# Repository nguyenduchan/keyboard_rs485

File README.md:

# Bàn phím công nghiệp All-in-One (PCB 120 × 120 mm)

Mạch **STM32G030F6P6 + RS485 (SIT3485)**, rev C — linh kiện phổ biến. **TM1638** quét 2 module LED 4 số, 8 LED trạng thái và 16 phím. Còi chủ động báo nhận phím. **Mặt trên (F.Cu):** toàn bộ **chip và SMD**, stencil một lần. **Mặt dưới (B.Cu):** chỉ **phím, LED 3 mm, 2 module 7 đoạn 4 số**. PCB đã đi dây 2 lớp (autorouter PathFinder, `tools/pathfinder.cpp`), DRC KiCad sạch. Cột phải tách **nguồn (trên)** và **MCU + RS485 (dưới)**. Chống phím ma: `docs/CHONG_PHIM_MA.md`.

## Cấu trúc thư mục

| Thư mục / file | Nội dung |
|----------------|----------|
| `docs/SO_DO_NGUYEN_LY.md` | Sơ đồ nguyên lý, ghép chân, netlist |
| `docs/PCB_LAYOUT.md` | Tọa độ mm, mặt trên / mặt dưới, checklist |
| `docs/CHONG_PHIM_MA.md` | Lọc ma trận, tách vùng nguồn |
| `hardware/kicad/panel-keyboard/tools/front_layout_spec.py` | **Chuẩn tọa độ mặt trước** |
| `docs/CONFIG_PROTOCOL.md`, `docs/RUNTIME_FORMAT.md` | giao thức cấu hình + bản đồ thanh ghi + khối cấu hình (cho PC app) |
| `firmware/` | firmware STM32G030F6P6 (xem `firmware/README.md`) |
| `hardware/bom.csv` | BOM |

## Đồng bộ schematic + PCB

```text
python hardware/kicad/panel-keyboard/tools/update_pcb_all.py
python hardware/kicad/panel-keyboard/tools/verify_front_layout.py
```

`update_pcb_all.py` gọi `migrate_front_tht.py` (một process/ref, tránh crash `pcbnew` trên Windows) rồi `fix_front_layout.py` + gán net.

(Đóng KiCad trước khi chạy.) Quy tắc: `.cursor/rules/kicad-schematic-pcb-sync.mdc`

---

## Phím và LED — mặt dưới (B.Cu)

KiCad vẽ trang với **Y tăng xuống dưới** (đỉnh hình = Y nhỏ). Từ trên xuống: **7-seg → khe CNC 8 mm → keypad**. LED trạng thái ở cột phải của cụm phím. Thân phím và LED hướng xuống mặt dưới.

Hai module 4 số 0,56" (5641AS, thân 50,4 × 19,0 mm, bước digit 12,7 mm) đặt tâm **X=40** trùng tâm keypad. Hàng chân cách 15,24 mm. Khe giữa mép dưới thân 7-seg và mép trên thân phím là **8 mm**.

| Y | 16 | 32 | 48 | 64 | | 80 |
|---:|:---:|:---:|:---:|:---:|:---|:---:|
| 12 | | | | | | D10 |
| 15 | DS1 module 4 số (digit 1–4, tâm X=40) | | | | | |
| 20 | | | | | | D11 |
| 28 | | | | | | D12 |
| 35 | DS2 module 4 số (digit 5–8, tâm X=40) | | | | | |
| 36 | | | | | | D13 |
| 44 | | | | | | D14 |
| 52 | | | | | | D15 |
| 59 | SW13 | SW14 | SW15 | SW16 | | |
| 60 | | | | | | D16 |
| 68 | | | | | | D17 |
| 75 | SW9 | SW10 | SW11 | SW12 | | |
| 91 | SW5 | SW6 | SW7 | SW8 | | |
| 107 | SW1 | SW2 | SW3 | SW4 | | |

### Kiểm tra layout

Script so PCB với `front_layout_spec.py` (dung sai **0,01 mm** — lỗ phay mặt tủ tính từ tọa độ này):

```text
python hardware/kicad/panel-keyboard/tools/verify_front_layout.py
```

Tiêu chí:

- 16 nút + 2 module 4 số + 8 LED đúng tọa độ  
- Khe **thân phím ↔ thân module 7-seg dưới (DS2)** ≥ **8 mm** (đủ lưỡi CNC khoảng 3 mm và gân mặt máy)

Chuẩn hóa footprint trên PCB: `tools/fix_front_layout.py` (sau `update_pcb_all.py`).

---

## Chip và SMD — mặt trên (F.Cu)

**U6 TM1638** (SOP-28) nằm dưới cột LED trạng thái, quét 7-seg, LED 3 mm và phím. **U1 STM32G030F6P6** ngay bên phải, nối 3 dây STB/CLK/DIO (kéo lên 4,7k). Còi **BZ1** mặt trên tại (40, 50). Cột phải **X ≈ 82…118** tách hai khối: nguồn phía trên, MCU + RS485 phía dưới. **J_PWR** (115, 16) và **J485** (115, 102) hướng ra **cạnh phải**.

| Vùng | X (mm) | Y (mm) | Nội dung |
|------|--------|--------|----------|
| Dưới LED trạng thái | 70–90 | 74–99 | U6 TM1638, CLED1–3, RSTB/RCLK/RDIO |
| MCU | 90–104 | 80–96 | U1, CVDD1, CNRST, J_SWD và J_LOG (không lắp) |
| Còi | 34–58 | 44–56 | BZ1, QBZ, RBZG |
| **BUCK_5V** | 82–118 | 4–46 | J_PWR, U4 XL1509 (SOP-8), L1, D8, C2, C22 |
| **24V_PROTECT** | 82–118 | 48–76 | C4, F1, FBIN, TVS1, DREV, U5 |
| **MCU_LOGIC** | 72–118 | 78–116 | U1, U3, J485 |

Chi tiết: `docs/PCB_LAYOUT.md`, `tools/zone_layout.py`.

---

## Cơ khí tủ

- Lỗ phay mặt tủ **theo biến thể** (số module 7 đoạn, số LED, số phím / bàn phím màng), mọi số đo nguyên mm, nhìn từ mặt tủ: `hardware/mechanical/cnc/` (DXF cho máy CNC, SVG, CSV, decal). Sinh và kiểm tra: `python hardware/kicad/panel-keyboard/tools/cnc_panel.py --check` — xem `docs/CNC_MAT_MAY.md`.  
- Chip nằm **mặt trên**. Mặt dưới chỉ có phím và LED, hướng ra mặt máy  

## Mở thiết kế

KiCad 10+: `hardware/kicad/panel-keyboard/panel-keyboard.kicad_pro`

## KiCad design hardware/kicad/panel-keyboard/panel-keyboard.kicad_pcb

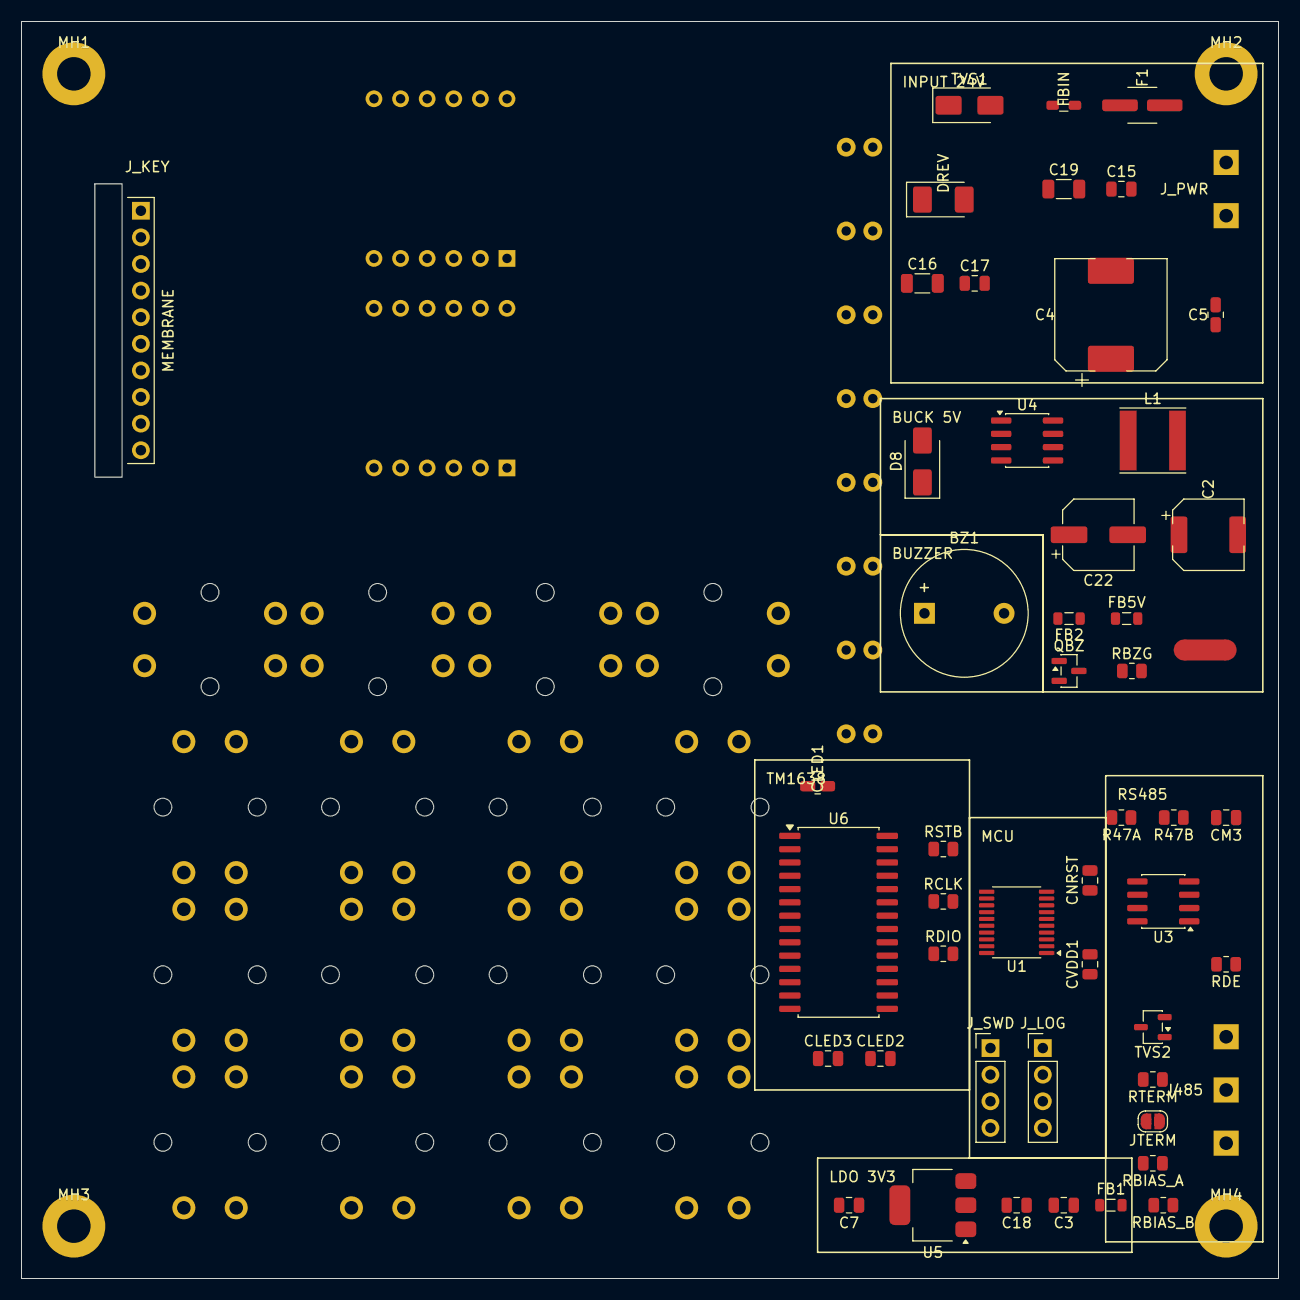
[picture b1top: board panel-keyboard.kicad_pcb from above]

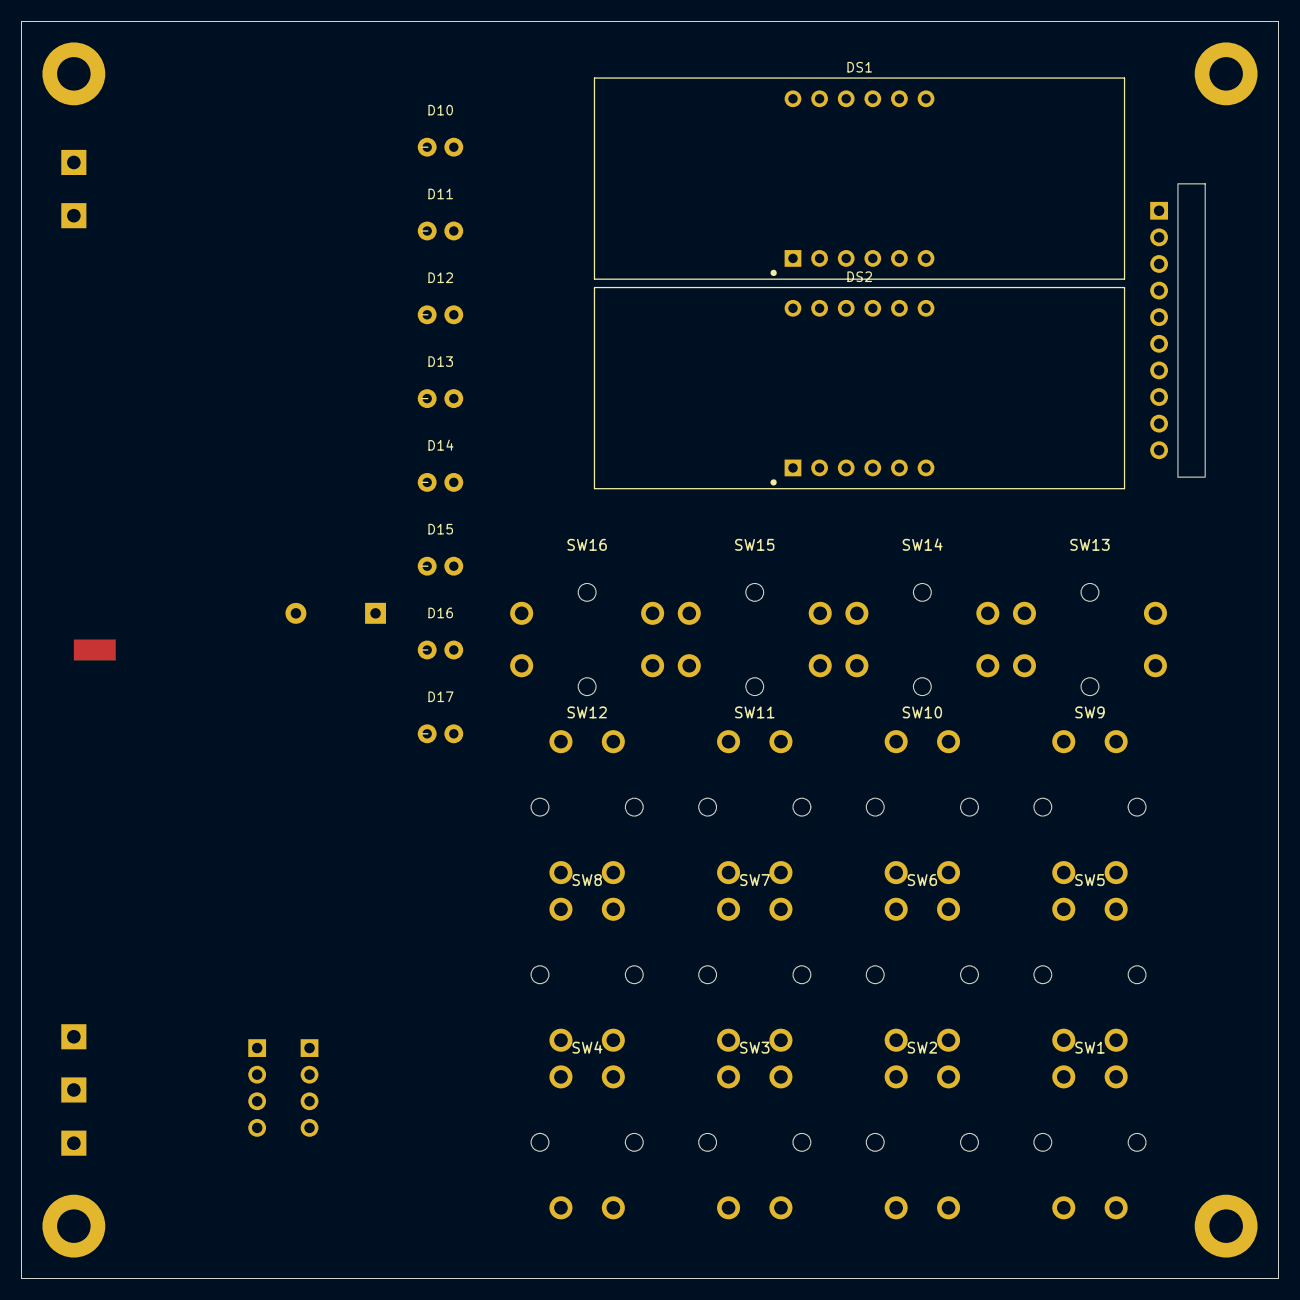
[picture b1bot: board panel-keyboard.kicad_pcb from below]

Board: 2 copper layers, 120.0 x 120.0 mm, 81 parts (26 on the bottom side), 49 nets, no tracks yet.

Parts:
BZ1: Active buzzer 5V 12x9.5; Buzzer_12x9.5RM7.6
C2, C22: 220uF 10V RVT1A221M0605; CP_Elec_6.3x5.4
C3: 22uF; C_0805_2012Metric
C4: 470uF 35V RVT1V471M1010; CP_Elec_10x10.5
C5, C18: 100nF; C_0805_2012Metric
C7: 10uF; C_0805_2012Metric
C15, C17: 100nF 50V; C_0805_2012Metric
C16, C19: 2.2uF 50V X7R; C_1206_3216Metric
CLED1, CLED2: 100nF; C_0805_2012Metric
CLED3: 10uF; C_0805_2012Metric
CM3: 100nF; C_0805_2012Metric
CNRST: 100nF; C_0805_2012Metric
CVDD1: 100nF; C_0805_2012Metric
D8: SS34; D_SMA
D10, D11, D12, D13, D14, D15, D16, D17: LED_3mm; LED_3mm_THT
DREV: SS34; D_SMA
DS1, DS2: 5641AS (4 digit 0.56in CC); Display_4digit_0.56in_THT
F1: mSMD050-33V (PPTC 0.5A 33V); Fuse_1812_4532Metric
FB1, FB2, FB5V: GZ2012D101TF 100R; L_0805_2012Metric
FBIN: GZ2012D601TF 600R; L_0805_2012Metric
J485: KF301-5.08-3P; TerminalBlock_3P_5.08
JTERM: 120R; SolderJumper-2_P1.3mm_Open_RoundedPad1.0x1.5mm
J_KEY: Membrane 1x10 2.54; Membrane_1x10_P2.54_Vertical_Slot
J_LOG: PinHeader_1x04_P2.54mm_Vertical
J_PWR: KF301-5.08-2P; TerminalBlock_2P_5.08
J_SWD: PinHeader_1x04_P2.54mm_Vertical
L1: SWPA6045S470MT 47uH; L_Taiyo-Yuden_NR-60xx
MH1, MH2, MH3, MH4: M3; MountingHole_M3
NT1: GND_STAR; NetTie-2_SMD_Pad2.0mm
QBZ: 2N7002; SOT-23
R47A, R47B: 47; R_0805_2012Metric
RBIAS_A: 560; R_0805_2012Metric
RBIAS_B: 560; R_0805_2012Metric
RBZG: 100k; R_0805_2012Metric
RCLK: 4.7k; R_0805_2012Metric
RDE: 10k; R_0805_2012Metric
RDIO: 4.7k; R_0805_2012Metric
RSTB: 4.7k; R_0805_2012Metric
RTERM: 120; R_0805_2012Metric
SW1, SW2, SW3, SW4, SW5, SW6, SW7, SW8, SW9, SW10, SW11, SW12, SW13, SW14, SW15, SW16: B3F-4055; SW_Tactile_12mm_THT
TVS1: SMAJ28CA; D_SMA
TVS2: PSM712-LF-T7; SOT-23-3
U1: STM32G030F6P6; TSSOP-20_4.4x6.5mm_P0.65mm
U3: SP3485EN; SOIC-8_3.9x4.9mm_P1.27mm
U4: XL1509-5.0E1; SOIC-8_3.9x4.9mm_P1.27mm
U5: AMS1117-3.3; SOT-223-3_TabPin2
U6: TM1638; SOIC-28W_7.5x17.9mm_P1.27mm

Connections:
+3V3: CM3.1, CVDD1.1, FB1.2, J_LOG.1, J_SWD.1, U1.4, U3.8
+3V3_LDO: C3.1, C18.1, FB1.1, U5.2
+5V: BZ1.1, C7.1, C22.1, FB2.2, FB5V.1, RBIAS_A.1, U5.3
+5V_LED: CLED1.1, CLED2.1, CLED3.1, FB5V.2, RCLK.1, RDIO.1, RSTB.1, U6.4, U6.15
+5V_RAW: C2.1, C5.1, FB2.1, L1.2, U4.3
+5V_SW: D8.1, L1.1, U4.2
+24V: C4.1, C16.1, C17.1, DREV.1, U4.1
+24V_FUSE: F1.2, FBIN.1
+24V_IN: F1.1, J_PWR.1
BZ_DRV: BZ1.2, QBZ.3
BZ_ON: QBZ.1, RBZG.1, U1.14
GND: C2.2, C3.2, C5.2, C7.2, C18.2, C22.2, CLED1.2, CLED2.2, CLED3.2, CM3.2, CNRST.2, CVDD1.2, J485.3, J_LOG.4, J_SWD.4, NT1.2, QBZ.2, RBIAS_B.2, RBZG.2, RDE.2, TVS2.3, U1.5, U3.5, U5.1, U6.18, U6.25
GND_PWR: C4.2, C15.2, C16.2, C17.2, C19.2, D8.2, J_PWR.2, NT1.1, TVS1.2, U4.4, U4.5, U4.6, U4.7, U4.8
GRID_1: D10.1, DS1.12, U6.24
GRID_2: D11.1, DS1.9, U6.23
GRID_3: D12.1, DS1.8, U6.22
GRID_4: D13.1, DS1.6, U6.21
GRID_5: D14.1, DS2.12, U6.20
GRID_6: D15.1, DS2.9, U6.19
GRID_7: D16.1, DS2.8, U6.17
GRID_8: D17.1, DS2.6, U6.16
KEY_K1: J_KEY.1, SW1.2, SW1.3, SW2.2, SW2.3, SW3.2, SW3.3, SW4.2, SW4.3, SW5.2, SW5.3, SW6.2, SW6.3, SW7.2, SW7.3, SW8.2, SW8.3, U6.1
KEY_K2: J_KEY.2, SW9.2, SW9.3, SW10.2, SW10.3, SW11.2, SW11.3, SW12.2, SW12.3, SW13.2, SW13.3, SW14.2, SW14.3, SW15.2, SW15.3, SW16.2, SW16.3, U6.2
LED_ROW: D10.2, D11.2, D12.2, D13.2, D14.2, D15.2, D16.2, D17.2, U6.13
LOG_RX: J_LOG.3, U1.1
LOG_TX: J_LOG.2, U1.20
MAX_DI: R47A.2, U3.4
MAX_RO: R47B.2, U3.1
NRST: CNRST.1, U1.6
RS485_A_BUS: J485.1, JTERM.1, RBIAS_A.2, TVS2.1, U3.6
RS485_B_BUS: J485.2, RBIAS_B.1, RTERM.2, TVS2.2, U3.7
RS485_DE: RDE.1, U1.8, U3.2, U3.3
RS485_TERM: JTERM.2, RTERM.1
SEG1: DS1.11, DS2.11, J_KEY.3, SW1.1, SW1.4, SW9.1, SW9.4, U6.5
SEG2: DS1.7, DS2.7, J_KEY.4, SW2.1, SW2.4, SW10.1, SW10.4, U6.6
SEG3: DS1.4, DS2.4, J_KEY.5, SW3.1, SW3.4, SW11.1, SW11.4, U6.7
SEG4: DS1.2, DS2.2, J_KEY.6, SW4.1, SW4.4, SW12.1, SW12.4, U6.8
SEG5: DS1.1, DS2.1, J_KEY.7, SW5.1, SW5.4, SW13.1, SW13.4, U6.9
SEG6: DS1.10, DS2.10, J_KEY.8, SW6.1, SW6.4, SW14.1, SW14.4, U6.10
SEG7: DS1.5, DS2.5, J_KEY.9, SW7.1, SW7.4, SW15.1, SW15.4, U6.11
SEG8: DS1.3, DS2.3, J_KEY.10, SW8.1, SW8.4, SW16.1, SW16.4, U6.12
SWCLK: J_SWD.3, U1.19
SWDIO: J_SWD.2, U1.18
TM_CLK: RCLK.2, U1.12, U6.27
TM_DIO: RDIO.2, U1.13, U6.26
TM_STB: RSTB.2, U1.11, U6.28
UART_RX: R47B.1, U1.10
UART_TX: R47A.1, U1.9
VIN_PROTECT: C15.1, C19.1, DREV.2, FBIN.2, TVS1.1

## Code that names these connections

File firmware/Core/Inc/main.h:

/* USER CODE BEGIN Header */
/**
  ******************************************************************************
  * @file           : main.h
  * @brief          : Header for main.c file.
  *                   This file contains the common defines of the application.
  ******************************************************************************
  * Bàn phím công nghiệp — Modbus RTU slave (STM32G030F6P6 + TM1638 + SIT3485)
  ******************************************************************************
  */
/* USER CODE END Header */

/* Define to prevent recursive inclusion -------------------------------------*/
#ifndef __MAIN_H
#define __MAIN_H

#ifdef __cplusplus
extern "C" {
#endif

/* Includes ------------------------------------------------------------------*/
#include "stm32g0xx_hal.h"

/* Private includes ----------------------------------------------------------*/
/* USER CODE BEGIN Includes */

/* USER CODE END Includes */

/* Exported types ------------------------------------------------------------*/
/* USER CODE BEGIN ET */

/* USER CODE END ET */

/* Exported constants --------------------------------------------------------*/
/* USER CODE BEGIN EC */

/* USER CODE END EC */

/* Exported macro ------------------------------------------------------------*/
/* USER CODE BEGIN EM */

/* USER CODE END EM */

/* Exported functions prototypes ---------------------------------------------*/
void Error_Handler(void);

/* USER CODE BEGIN EFP */

/* USER CODE END EFP */

/* Private defines -----------------------------------------------------------*/
#define TM_STB_Pin GPIO_PIN_4
#define TM_STB_GPIO_Port GPIOA
#define TM_CLK_Pin GPIO_PIN_5
#define TM_CLK_GPIO_Port GPIOA
#define TM_DIO_Pin GPIO_PIN_6
#define TM_DIO_GPIO_Port GPIOA
#define BZ_ON_Pin GPIO_PIN_7
#define BZ_ON_GPIO_Port GPIOA

/* USER CODE BEGIN Private defines */

/* USER CODE END Private defines */

#ifdef __cplusplus
}
#endif

#endif /* __MAIN_H */
